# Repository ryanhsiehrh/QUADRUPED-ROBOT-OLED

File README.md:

# QUADRUPED-ROBOT-OLED
Quadruped robot powered by an Arduino Pro Micro (ATmega32U4). Operates on 5V power, utilizing 12 servo motors for inverse kinematics and an animated OLED display face through Software I2C.

##  What it does

* **Inverse Kinematics:** Calculates real-time 3D leg positions ($X, Y, Z$) across 12 servos (3 per leg) for smooth walking, turning, and custom body movements.
* **Animated OLED Face:** Runs an expression state machine on a 0.96 inch OLED display. The eyes pan side-to-side, blink every 3 seconds, and automatically close when the robot sits down.
* **Software I2C Communication:** Since the Pro Micro's hardware I2C pins (Pins 2 & 3) were already being used for servo signal lines, the OLED screen is driven via software I2C on analog pins `A0` (SDA) and `A1` (SCL).
* **50Hz Servo Interrupts:** Uses `FlexiTimer2` to keep servo updates running smoothly in the background without locking up the loop.
* **USB Serial Control:** Responds to string commands sent from the Arduino Serial Monitor at 9600 baud.

---

##  Hardware Setup & Pin Mapping

### Electronics
* **Board:** Arduino Pro Micro (ATmega32U4, 5V / 16MHz)
* **Servos:** 12x SG90 Micro Servos
* **Display:** 0.96" SSD1306 OLED Screen ($128 \times 64$, Yellow/Blue split)
* **Power:** External 5V power supply for the servos (common ground connected to the Arduino).
* **LM2596S Step Down Module** used to step down 12V power supply to 5V if needed

### Pinout Table

| Component | Function | Arduino Pro Micro Pin |
| :--- | :--- | :--- |
| **OLED Display** | **SDA** (Data) | **A0** *(Software I2C)* |
| **OLED Display** | **SCL** (Clock) | **A1** *(Software I2C)* |
| **Leg 0 (Back Left)** | Coxa / Femur / Tibia | Pins `2`, `3`, `4` |
| **Leg 1 (Front Left)**| Coxa / Femur / Tibia | Pins `5`, `6`, `7` |
| **Leg 2 (Back Right)** | Coxa / Femur / Tibia | Pins `8`, `9`, `10` |
| **Leg 3 (Front Right)**  | Coxa / Femur / Tibia | Pins `16`, `14`, `15` |

---

## PCB Design

* Simple 2-layer design with a solid ground plane on the back
* Uses barrel jack for power connection
* Specific area to hold the LM2596S Step Down Module
* Contains SPDT switch to toggle power to servo motors ON or OFF

**Schematic:**

**PCB:**

---

##  Serial Commands

Set your Serial Monitor to **9600 Baud** and **Newline**. Type any of the following commands:

* `w 0 1` – Stand Up (wakes up face display)
* `w 0 0` – Sit Down (closes eyes on display)
* `w 1 x` – Walk Forward x steps
* `w 2 x` – Walk Backward x steps
* `w 3 x` – Turn Right x steps
* `w 4 x` – Turn Left x steps
* `w 5 x` – Hand Shake emote (x times)
* `w 6 x` – Hand Wave emote (x times)
* `w 7 x` – Side-to-Side body sway (x times)
* `w 8 x` – Bounce body emote (x times)
* `w 9 x` – Up and Down stretch (x times)

---

## Libraries

Install these via the Arduino Library Manager or online:

* `U8g2` (for operating OLED screen)
* `FlexiTimer2` (for 50Hz timer interrupts)
* `SerialCommand` (for parsing serial input strings)
* `Servo` (standard servo motor library)

---

## 3D Printed Parts

The chassis and leg components are based on [Regis Hsu's Spider Robot Design on Thingiverse](https://www.thingiverse.com/thing:1009659).

---

## How to Run

1. **Center Servos:** Before attaching the legs, upload `servo_90.ino` to set all 12 servos to their $90^\circ$ midpoint.
2. **Assemble:** Mount the leg horns at $90^\circ$ angles relative to the chassis.
3. **Upload Firmware:** Open `QUADRUPED-ROBOT-OLED.ino`, select **Arduino Leonardo**, and flash the sketch.
4. **Test:** Open Serial Monitor, make sure Newline is enabled, and send `w 0 1` to stand the robot up!

---

## Demo Video
[Watch the Quadruped Robot video here!](https://www.youtube.com/watch?v=7HYvcp7Kx8c)

---

## Credits

* Original base code by panerqiang@sunfounder.com (2015).
* Bluetooth remote and emote modifications by **RegisHsu** (2015).
* Pro Micro migration, custom movement emotes, software I2C OLED face animation, Kicad schematic and PCB developed by **Ryan Hsieh**.

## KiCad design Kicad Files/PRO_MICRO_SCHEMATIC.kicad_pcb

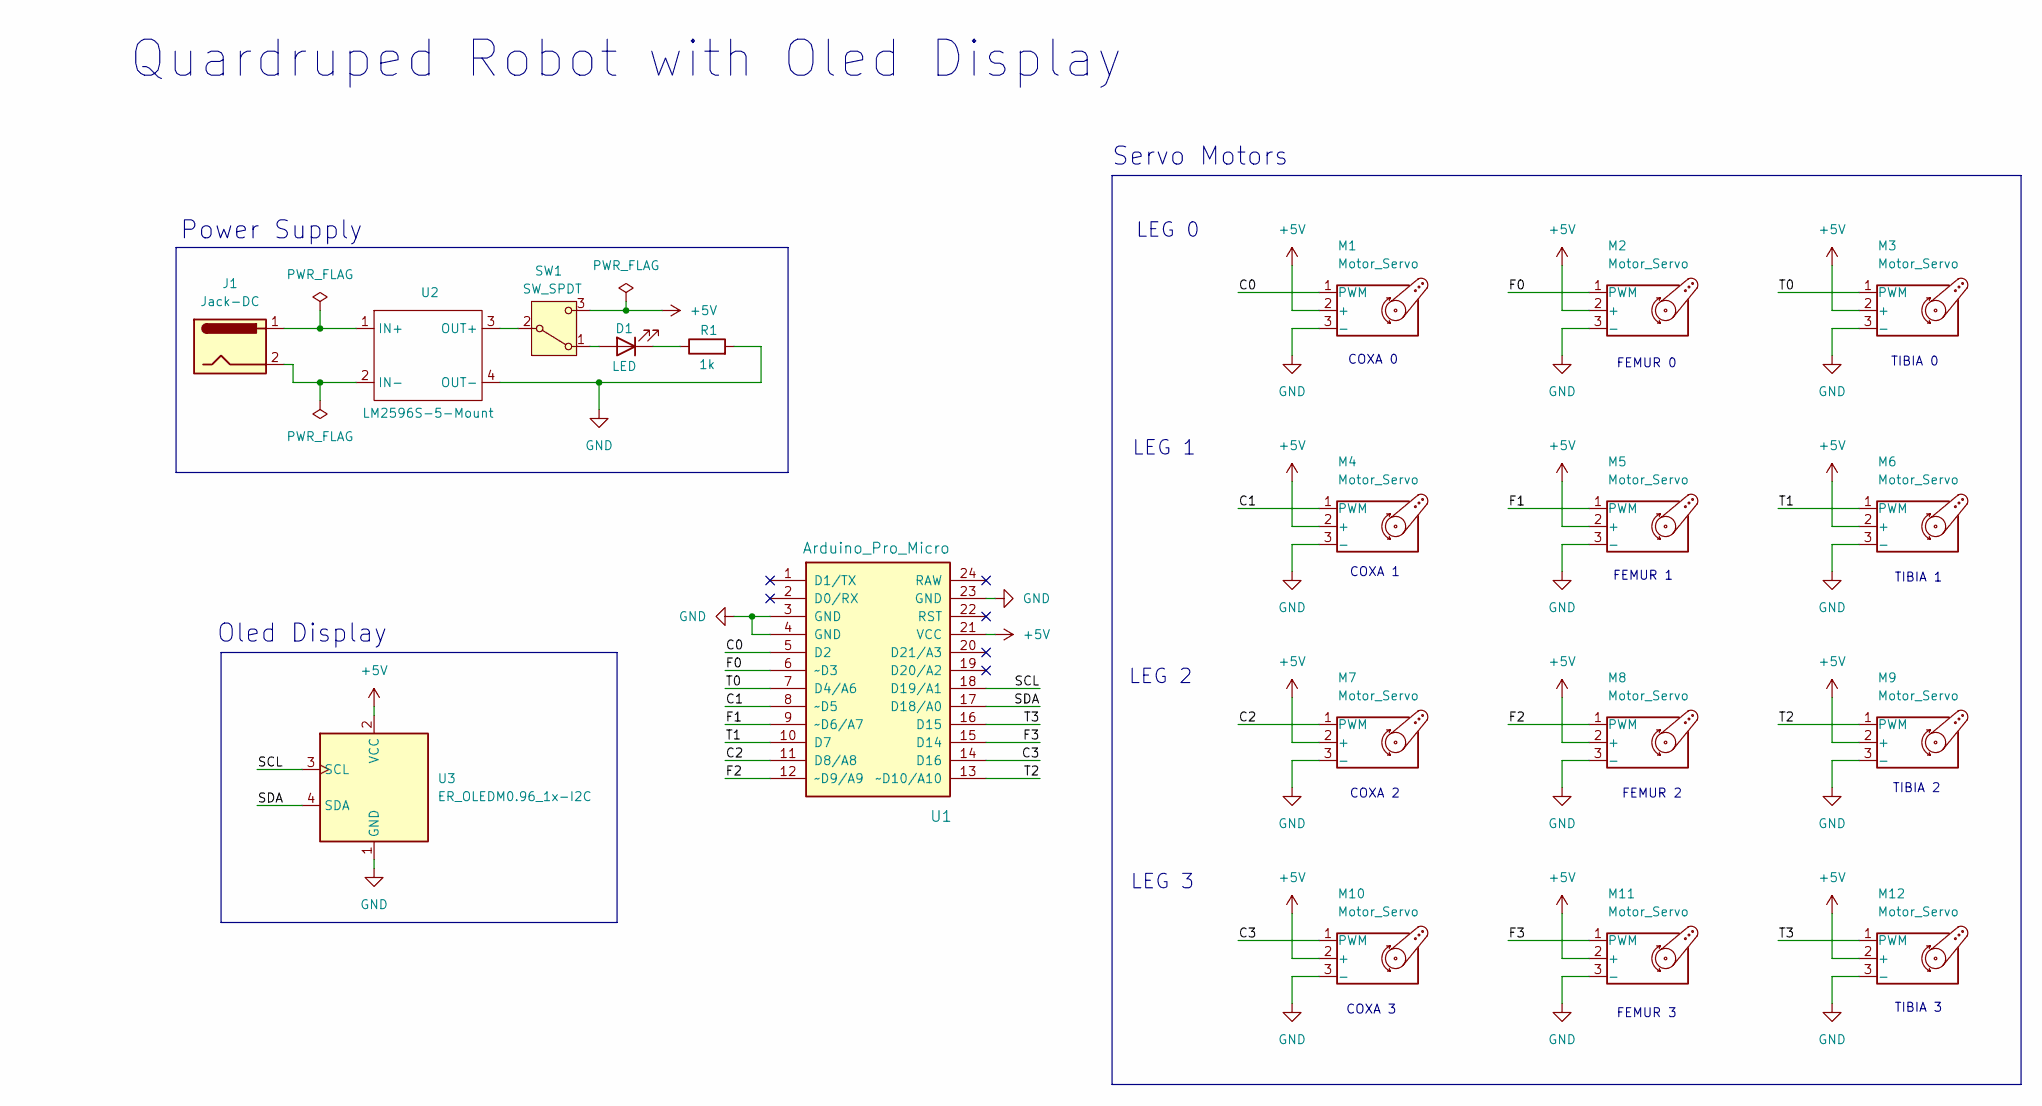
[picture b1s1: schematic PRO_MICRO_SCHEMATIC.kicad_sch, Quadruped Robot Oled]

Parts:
D1: LED; LED_D3.0mm
J1: Jack-DC; BarrelJack_Horizontal
M1, M2, M3, M4, M5, M6, M7, M8, M9, M10, M11, M12: Motor_Servo; PinHeader_1x03_P2.54mm_Vertical
R1: 1k; R_Axial_DIN0411_L9.9mm_D3.6mm_P12.70mm_Horizontal
SW1: SW_SPDT; SW_E-Switch_EG1271_SPDT
U1: Arduino_Pro_Micro; Sparkfun_Pro_Micro
U2: LM2596S-5-Mount
U3: ER_OLEDM0.96_1x-I2C; PinSocket_1x04_P2.54mm_Vertical

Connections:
+5V: M1.2 (+), M2.2 (+), M3.2 (+), M4.2 (+), M5.2 (+), M6.2 (+), M7.2 (+), M8.2 (+), M9.2 (+), M10.2 (+), M11.2 (+), M12.2 (+), SW1.3 (C), U1.21 (VCC), U3.2 (VCC)
/C0: M1.1 (PWM), U1.5 (D2)
/C1: M4.1 (PWM), U1.8 (~D5)
/C2: M7.1 (PWM), U1.11 (D8/A8)
/C3: M10.1 (PWM), U1.14 (D16)
/F0: M2.1 (PWM), U1.6 (~D3)
/F1: M5.1 (PWM), U1.9 (~D6/A7)
/F2: M8.1 (PWM), U1.12 (~D9/A9)
/F3: M11.1 (PWM), U1.15 (D14)
/SCL: U1.18 (D19/A1), U3.3 (SCL)
/SDA: U1.17 (D18/A0), U3.4 (SDA)
/T0: M3.1 (PWM), U1.7 (D4/A6)
/T1: M6.1 (PWM), U1.10 (D7)
/T2: M9.1 (PWM), U1.13 (~D10/A10)
/T3: M12.1 (PWM), U1.16 (D15)
GND: M1.3 (-), M2.3 (-), M3.3 (-), M4.3 (-), M5.3 (-), M6.3 (-), M7.3 (-), M8.3 (-), M9.3 (-), M10.3 (-), M11.3 (-), M12.3 (-), R1.2, U1.3 (GND), U1.4 (GND), U1.23 (GND), U2.4 (OUT-), U3.1 (GND)
unnamed: D1.2 (A), SW1.1 (A)
unnamed: D1.1 (K), R1.1
unnamed: SW1.2 (B), U2.3 (OUT+)
unnamed: J1.1, U2.1 (IN+)
unnamed: J1.2, U2.2 (IN-)

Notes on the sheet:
FEMUR 3
Oled Display
Quardruped Robot with Oled Display
TIBIA 3
LEG 0
FEMUR 0
COXA 1
LEG 3
TIBIA 0
FEMUR 2
FEMUR 1
COXA 3
COXA 0
Power Supply
TIBIA 2
TIBIA 1
LEG 1
Servo Motors
COXA 2
LEG 2

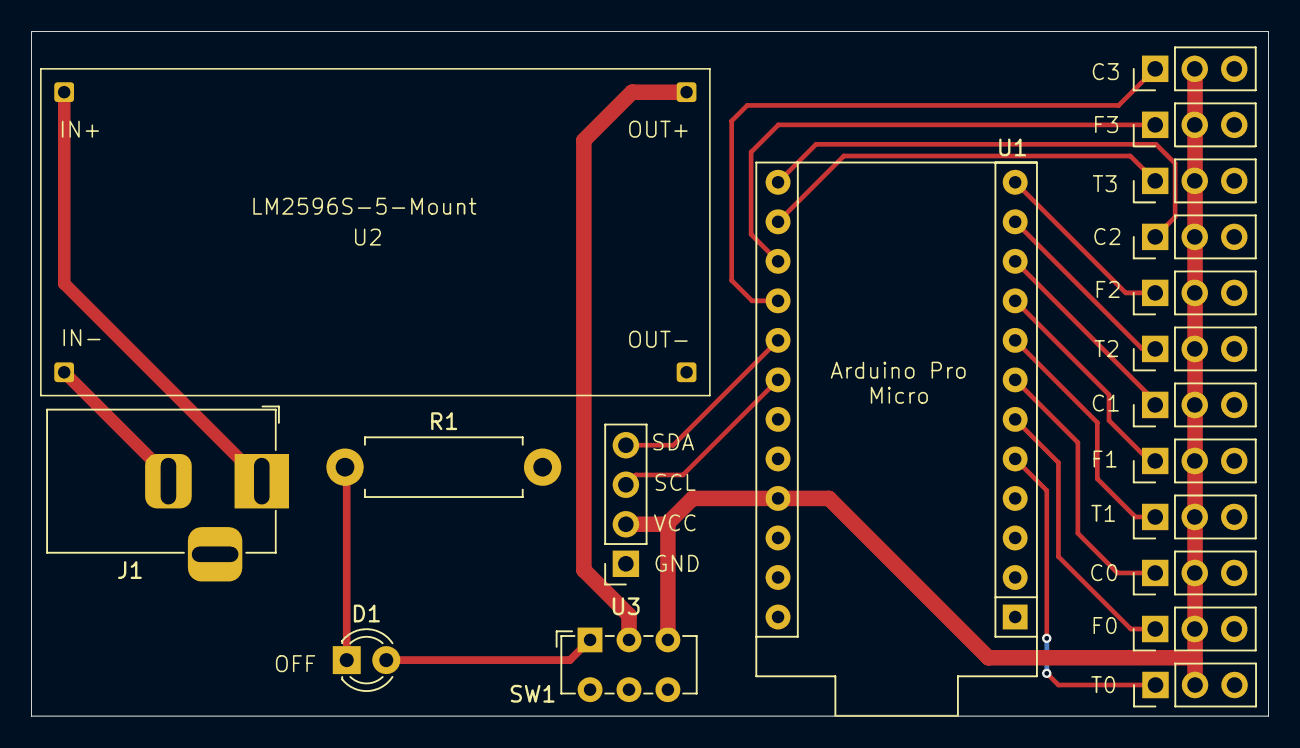
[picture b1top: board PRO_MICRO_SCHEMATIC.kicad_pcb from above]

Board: 2 copper layers, 79.5 x 44.0 mm, 19 parts (0 on the bottom side), 21 nets.
